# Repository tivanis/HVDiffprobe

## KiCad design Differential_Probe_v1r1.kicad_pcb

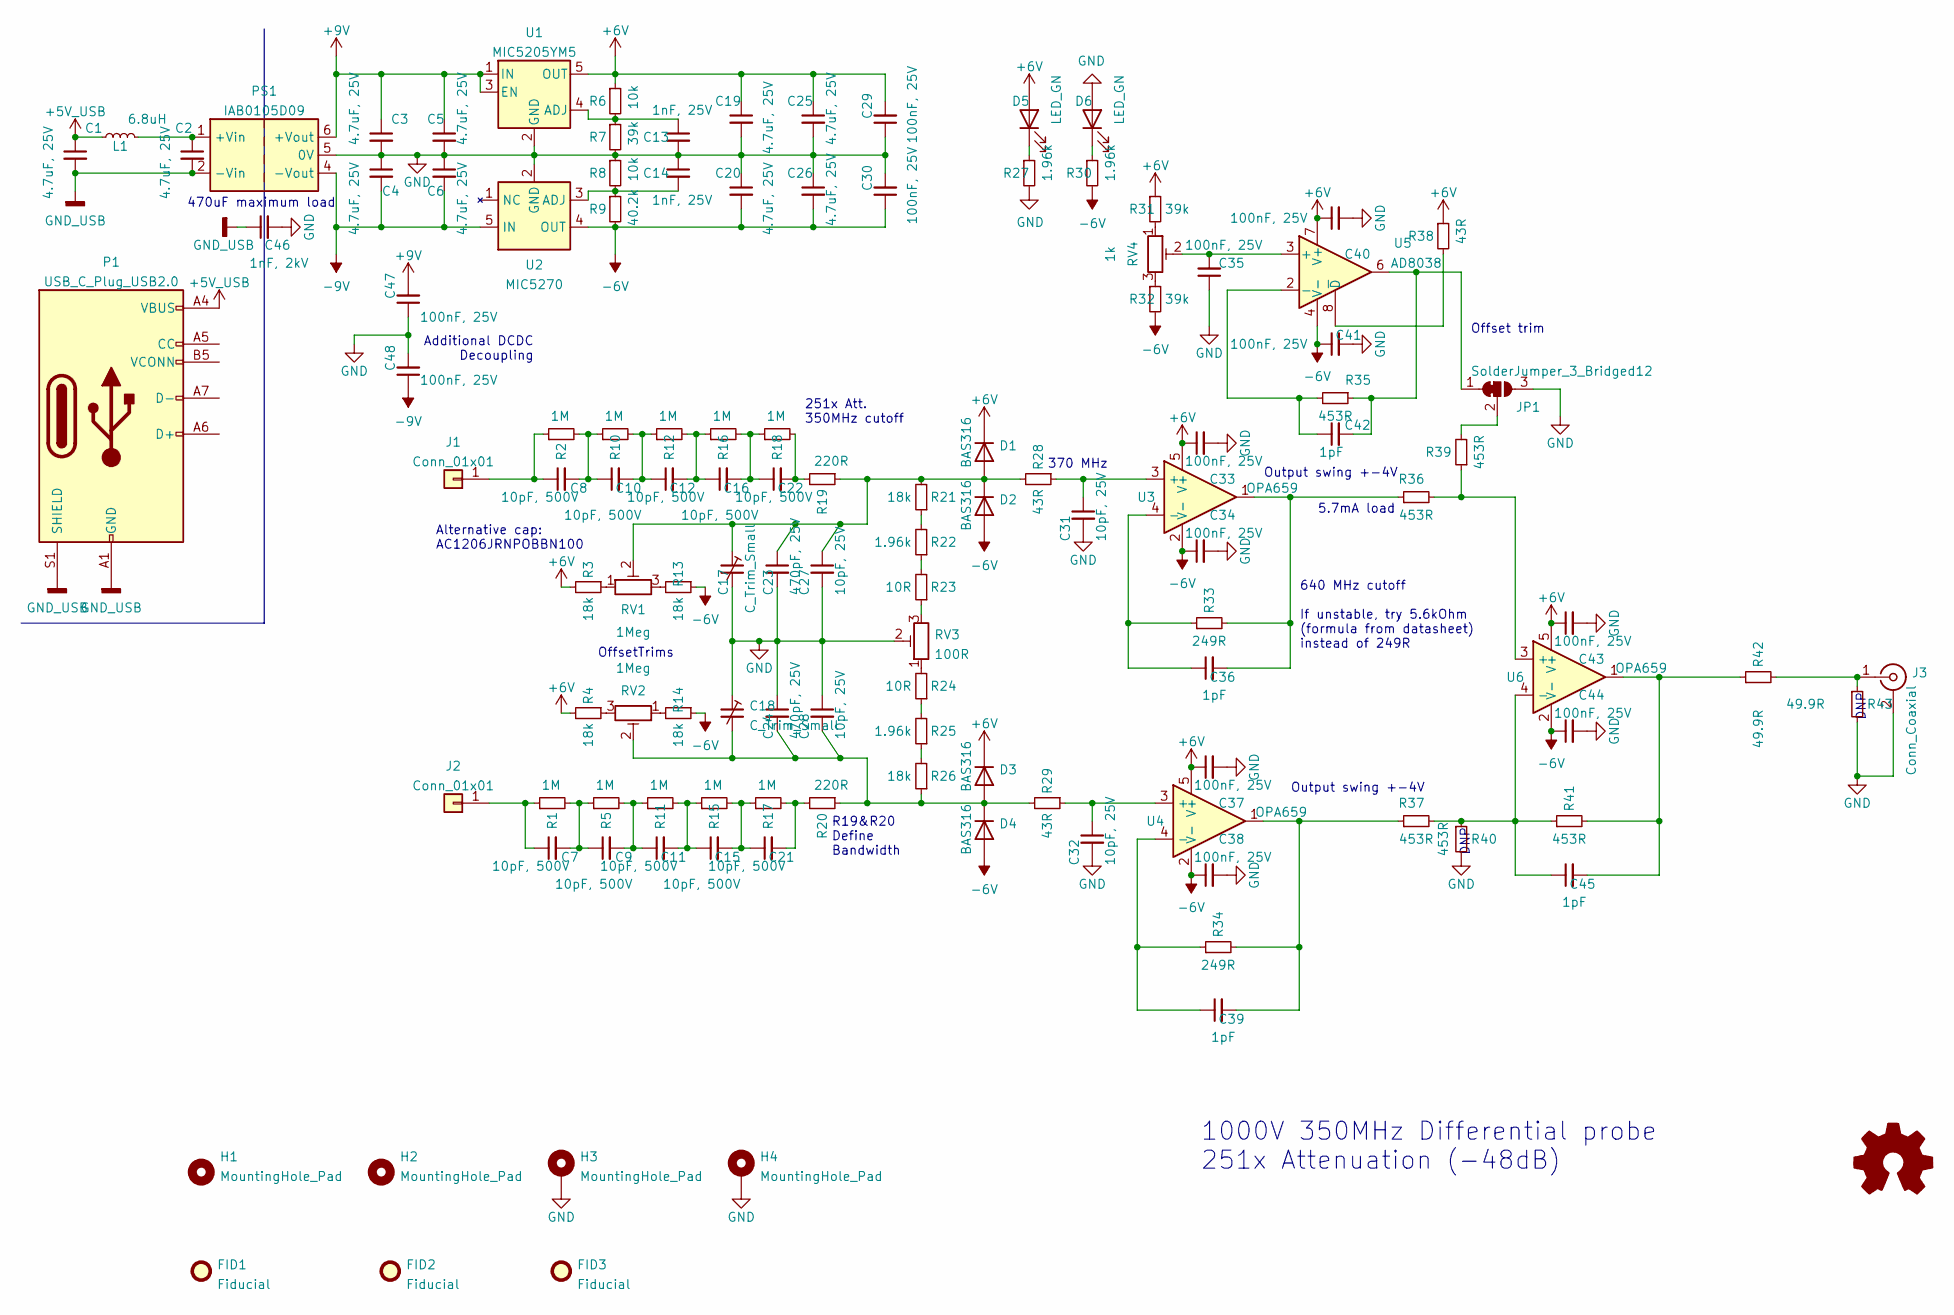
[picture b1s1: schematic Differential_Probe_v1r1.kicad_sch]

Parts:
C1, C2, C3, C4, C5, C6, C19, C20, C25, C26: 4.7uF, 25V; C_0805_2012Metric; Manufacturer Part Number TMK212BBJ475KGHT
C7, C8, C9, C10, C11, C12, C15, C16, C21, C22: 10pF, 500V; C_1206_3216Metric; Manufacturer Part Number 1206N100G501CT
C13, C14: 1nF, 25V; C_0603_1608Metric; Manufacturer Part Number C0603C102K3RAC
C17, C18: C_Trim_Small; C_Trimmer_Voltronics_JZ; Manufacturer Part Number JZ400
C23, C24: 470pF, 25V; C_0603_1608Metric; Manufacturer Part Number VJ0603A471GXXCW1BC
C27, C28, C31, C32: 10pF, 25V; C_0603_1608Metric; Manufacturer Part Number CL03C100DA3GNNC
C29, C30, C33, C34, C35, C37, C38, C40, C41, C43, C44, C47, C48: 100nF, 25V; C_0603_1608Metric; Manufacturer Part Number CC0603MRX7R8BB104
C36, C39, C42, C45: 1pF; C_0603_1608Metric; Manufacturer Part Number 06033A1R0CAT2A
C46: 1nF, 2kV; C_1812_4532Metric_Pad1.57x3.40mm_HandSolder; Manufacturer Part Number VJ2008Y102KXUSTX1
D1, D2, D3, D4: BAS316; D_SOD-323; Manufacturer Part Number BAS316,135
D5, D6: LED_GN; LED_0603_1608Metric; Manufacturer Part Number APT1608SGC
FID1, FID2, FID3: Fiducial; Fiducial_0.5mm_Mask1mm
H1, H2: MountingHole_Pad; MountingHole_3.2mm_M3
H3, H4: MountingHole_Pad; MountingHole_3.2mm_M3_Pad_Via
J1, J2: Conn_01x01; MountingHole_2.2mm_M2_Pad_Via
J3: Conn_Coaxial; BNC_MOLEX_73100-0154_Horizontal; Manufacturer Part Number 73100-0154
JP1: SolderJumper_3_Bridged12; SolderJumper-3_P1.3mm_Open_RoundedPad1.0x1.5mm
L1: 6.8uH; L_1008_2520Metric; Manufacturer Part Number VLS201610HBX-6R8M-1
P1: USB_C_Plug_USB2.0; USB_C_Receptacle_GCT_USB4085; Manufacturer Part Number USB4085-GF-A
PS1: IAB0105D09; Converter_DCDC_XP_POWER-IAxxxxS_THT; Manufacturer Part Number IAB0105D09
R1, R2, R5, R10, R11, R12, R15, R16, R17, R18: 1M; R_1206_3216Metric; Manufacturer Part Number KTR18EZPF1004
R3, R4, R13, R14, R21, R26: 18k; R_0603_1608Metric; Manufacturer Part Number CR0603-FX-1802ELF
R6, R8: 10k; R_0603_1608Metric; Manufacturer Part Number CR0603-FX-1501ELF
R7, R31, R32: 39k; R_0603_1608Metric; Manufacturer Part Number CR0603-FX-3902ELF
R9: 40.2k; R_0603_1608Metric; Manufacturer Part Number CR0603-FX-1501ELF
R19, R20: 220R; R_0603_1608Metric; Manufacturer Part Number ERJ-PA3F2200V
R22, R25, R27, R30: 1.96k; R_0603_1608Metric; Manufacturer Part Number CR0603-FX-1961ELF
R23, R24: 10R; R_0603_1608Metric; Manufacturer Part Number CR0603-FX-10R0ELF
R28, R29, R38: 43R; R_0603_1608Metric; Manufacturer Part Number CR0603-FX-43R0ELF
R33, R34: 249R; R_0603_1608Metric; Manufacturer Part Number CR0603-FX-2490ELF
R35, R36, R37, R39, R40, R41: 453R; R_0603_1608Metric; Manufacturer Part Number CR0603-FX-4530ELF
R42, R43: 49.9R; R_0603_1608Metric; Manufacturer Part Number CR0603-FX-43R0ELF
RV1, RV2: 1Meg; Potentiometer_Bourns_3314G_Vertical; Manufacturer Part Number TC33X-2-105G
RV3: 100R; Potentiometer_Bourns_3314G_Vertical; Manufacturer Part Number TC33X-2-101E
RV4: 1k; Potentiometer_Bourns_3314G_Vertical; Manufacturer Part Number TC33X-2-103G
U1: MIC5205YM5; SOT-23-5; Manufacturer Part Number MIC5205YM5
U2: MIC5270; SOT-23-5; Manufacturer Part Number MIC5270YM5-TR
U3, U4, U6: OPA659; SOT-23-5; Manufacturer Part Number OPA659IDBVT
U5: AD8038; SOIC-8_3.9x4.9mm_P1.27mm

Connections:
+5V_USB: C1.1, L1.1, P1.A4 (VBUS), P1.A9 (VBUS), P1.B4 (VBUS), P1.B9 (VBUS)
+6V: C19.1, C25.1, C29.2, C33.1, C37.1, C40.1, C43.1, D1.1 (K), D3.1 (K), D5.2 (A), R3.2, R4.2, R6.1, R31.1, R38.1, U1.5 (OUT), U3.5 (V+), U4.5 (V+), U5.7 (V+), U6.5 (V+)
+9V: C3.1, C5.1, C47.2, PS1.6 (+Vout), U1.1 (IN), U1.3 (EN)
-6V: C20.2, C26.2, C30.1, C34.1, C38.1, C41.1, C44.1, D2.2 (A), D4.2 (A), R9.2, R13.1, R14.1, R30.2, R32.2, U2.4 (OUT), U3.2 (V-), U4.2 (V-), U5.4 (V-), U6.2 (V-)
-9V: C4.2, C6.2, C48.1, PS1.4 (-Vout), U2.5 (IN)
GND: C3.2, C4.1, C5.2, C6.1, C13.2, C14.1, C17.2, C18.1, C19.2, C20.1, C23.2, C24.1, C25.2, C26.1, C27.2, C28.1, C29.1, C30.2, C31.2, C32.2, C33.2, C34.2, C35.1, C37.2, C38.2, C40.2, C41.2, C43.2, C44.2, C46.2, C47.1, C48.2, D6.2 (A), H3.1, H4.1, J3.2 (Ext), JP1.3 (B), PS1.5 (0V), R7.2, R8.1, R27.2, R40.2, R43.2, RV3.2, U1.2 (GND), U2.2 (GND)
GND_USB: C1.2, C2.2, C46.1, P1.A1 (GND), P1.A12 (GND), P1.B1 (GND), P1.B12 (GND), P1.S1 (SHIELD), PS1.2 (-Vin)
unnamed: C2.1, L1.2, PS1.1 (+Vin)
unnamed: C7.1, J2.1, R1.1
unnamed: C7.2, C9.1, R1.2, R5.1
unnamed: C8.1, J1.1, R2.1
unnamed: C8.2, C10.1, R2.2, R10.1
unnamed: C10.2, C12.1, R10.2, R12.1
unnamed: C9.2, C11.1, R5.2, R11.1
unnamed: C11.2, C15.1, R11.2, R15.1
unnamed: C12.2, C16.1, R12.2, R16.1
unnamed: C13.1, R6.2, R7.1, U1.4 (ADJ)
unnamed: C14.2, R8.2, R9.1, U2.3 (ADJ)
unnamed: C15.2, C21.1, R15.2, R17.1
unnamed: C16.2, C22.1, R16.2, R18.1
unnamed: C17.1, C23.1, C27.1, D1.2 (A), D2.1 (K), R19.1, R21.2, R28.2, RV1.2
unnamed: C18.2, C24.2, C28.2, D3.2 (A), D4.1 (K), R20.1, R26.1, R29.2, RV2.2
unnamed: C21.2, R17.2, R20.2
unnamed: C22.2, R18.2, R19.2
unnamed: C31.1, R28.1, U3.3 (+)
unnamed: C32.1, R29.1, U4.3 (+)
unnamed: C35.2, RV4.2, U5.3 (+)
unnamed: C36.1, R33.1, U3.4 (-)
unnamed: C36.2, R33.2, R36.1, U3.1
unnamed: C39.1, R34.1, U4.4 (-)
unnamed: C39.2, R34.2, R37.1, U4.1
unnamed: C42.1, R35.2, U5.2 (-)
unnamed: C42.2, JP1.1 (A), R35.1, U5.6
unnamed: C45.1, R37.2, R40.1, R41.1, U6.4 (-)
unnamed: C45.2, R41.2, R42.1, U6.1
unnamed: D5.1 (K), R27.1
unnamed: D6.1 (K), R30.1
unnamed: J3.1 (In), R42.2, R43.1
unnamed: JP1.2 (C), R39.2
unnamed: R3.1, RV1.1
unnamed: R4.1, RV2.3
unnamed: R13.2, RV1.3
unnamed: R14.2, RV2.1
unnamed: R21.1, R22.2
unnamed: R22.1, R23.2
unnamed: R23.1, RV3.3
unnamed: R24.1, R25.2
unnamed: R24.2, RV3.1
unnamed: R25.1, R26.2
unnamed: R31.2, RV4.1
unnamed: R32.1, RV4.3
unnamed: R36.2, R39.1, U6.3 (+)
unnamed: R38.2, U5.8 (~D)

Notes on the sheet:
370 MHz
470uF maximum load
R19&R20 Define Bandwidth
DNP
Offset trim
1000V 350MHz Differential probe 251x Attenuation (-48dB)
5.7mA load
Additional DCDC Decoupling
Alternative cap: AC1206JRNPOBBN100
Output swing +-4V
640 MHz cutoff If unstable, try 5.6kOhm (formula from datasheet) instead of 249R
251x Att. 350MHz cutoff
OffsetTrims

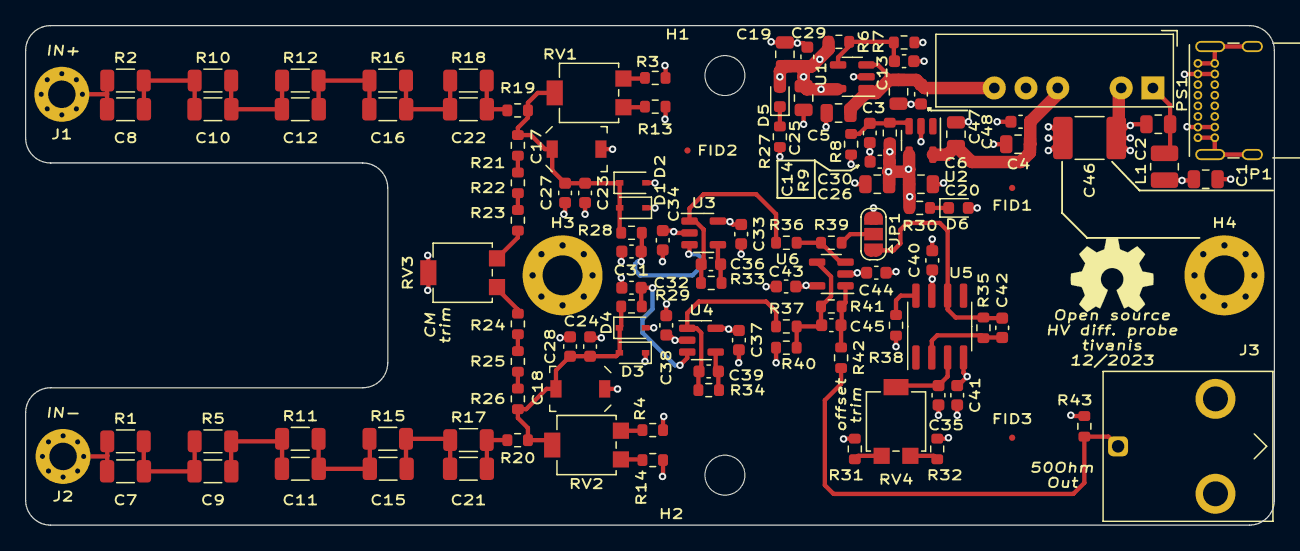
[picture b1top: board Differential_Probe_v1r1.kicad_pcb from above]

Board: 4 copper layers, 100.0 x 40.0 mm, 121 parts (0 on the bottom side), 53 nets.
